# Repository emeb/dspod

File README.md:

# dspod

dspod is a small ecosystem of audio DSP boards

The collection consists of the following hardware

* [dspod_module](./dspod_module) - a motherboard / carrier that adapts the standard dspod pinout
  for Eurorack, including power, I/O level buffers and user interface.
* [dspod_cv1800b](./dspod_cv1800b) - a daughterboard comprising a Sophgo/CVItek CV1800B Linux SoC
  with 64MB RAM, SD card interface, USB and GPIO + audio I/O.
* [dspod_rp2350](./dspod_rp2350) - a daughterboard with a Raspberry Pi RP2350, 4MB flash, 8MB PSRAM, USB, GPIO and audio I/O.
* [dspod_esp32s3](./dspod_esp32s3) - a daughterboard with an ESP32 S3 processor, 4MB flash, 2MB PSRAM, USB, RF, GPIO and audio I/O.
* [dspod_h7r3](./dspod_h7r3) - a daughterboard with an STM32H7R3V8 MCU, QSPI flash or PSRAM, USB, GPIO and audio I/O
* [dspod_u3c5](dspod_u3c5) - a daughterboard with an STM32U3C5RI MCU, QSPI PSRAM, USB, GPIO and audio I/O.
* [dspod_up5k](dspod_up5k) - a daughterboard with an iCE40UP5k FPGA, Flash, PSRAM, ADC, GPIO and audio I/O.
* [dspod_stampp4](./dspod_stampp4) - a daughterboard with an ESP32 P4 MCU, 16MB flash, 32MB PSRAM, USB, GPIO and Audio I/O

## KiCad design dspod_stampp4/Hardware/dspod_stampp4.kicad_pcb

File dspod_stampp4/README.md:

# dspod_stampp4

The dspod_stampp4 is an audio daughterboard based on the M5Stack Stamp P4 which provides an ESP32P4 MCU with 16MB Flash, 32MB PSRAM, USB and GPIO. The M5Stack module is used because the bare ESP32P4 devices were not available from the usual hobbyist distribution channels at the time of development. The primary motivation was to see if the faster dual-core RISC V architecture provided any meaningful performance benefit.

## Abstract

This board is a small 32-pin device with the following features:

* M5Stack Stamp P4 module containing 
  - ESP32S3H4R2 MCU
    - 68-pin QFN package
    - Dual-core RISC V CPUs 
    - 768kB SRAM
    - 32MB PSRAM in package
    - USB, I2C, SPI, ADC, GPIO, etc on-chip
  - 16MB QSPI flash
  - USB-C Connector for development
  - Various connectors for MIPI, SD
* Nuvoton NAU88C22 stereo codec
* Misc GPIO
  - SPI
  - I2C
  - GPIO
* Four channels of 3.3V multiplexed A/D input

## Design Materials

* [Schematic](./doc/dspod_stampp4_sch.pdf)

## Hardware

The hardware design is provided in Kicad 9.x format in the [Hardware](./Hardware) directory.

## Firmware

Firmware is available in the [Firmware](./Firmware) directory.

## Results

The hardware implementation is very similar to the [dspod_esp32s3](../dspod_esp32s3/README.md) so there weren't any big surprises in the overall performance. The encoder/button/LCD-based UI is virtually identical to that on the other three dspod projects so it feels pretty much the same regardless of which instance is in use. The basic effects - filters, delays, reverbs, pitch, frequency and phase shifts - all work the same way and use roughly the right amount of CPU based on their complexity. Some minor changes were required to the ADC and I2S hardware driver code due to the differences between ESP-IDF V5.x and V6.x, as well as migrating from Extensa to RISC-V CPU architecture.

Overall, the faster CPU cores (360MHz RISC V vs 240MHz Extensa LX7 on the ESP32 S3) didn't make a huge difference in DSP performance and the modest speedup in the algorithms that run exclusively from on-chip memory wouldn't be a strong motivator for choosing the P4 vs the S3.

Hardware-wise, using the pre-build module with castellated pads presented some additional assembly challenges, most notably that the module does not fit between the  two rows of pin headers in the dspod physical standard so it was necessary to use SMT pin headers soldered to the bottom side of the board which was difficult to align properly in order to ensure the board would plug into the dspod_module. That aside, having all the small SMT components pre-assembled on the module did make frontside assembly much simpler.

## Going Further

While I've explored most of the highlights, there are a few aspects of this MCU I'd like to explore further:

#### CPU Cores

Pushing the RISC V CPU cores harder and trying some of the more advanced math features would be interesting.

#### Algorithms

The current complement of effects algorithms are fairly lightweight so I'm looking forward to trying out some more complex things, and while spectral processing is probably not practical, there is CPU bandwidth and RAM capacity for more complex time domain effects.

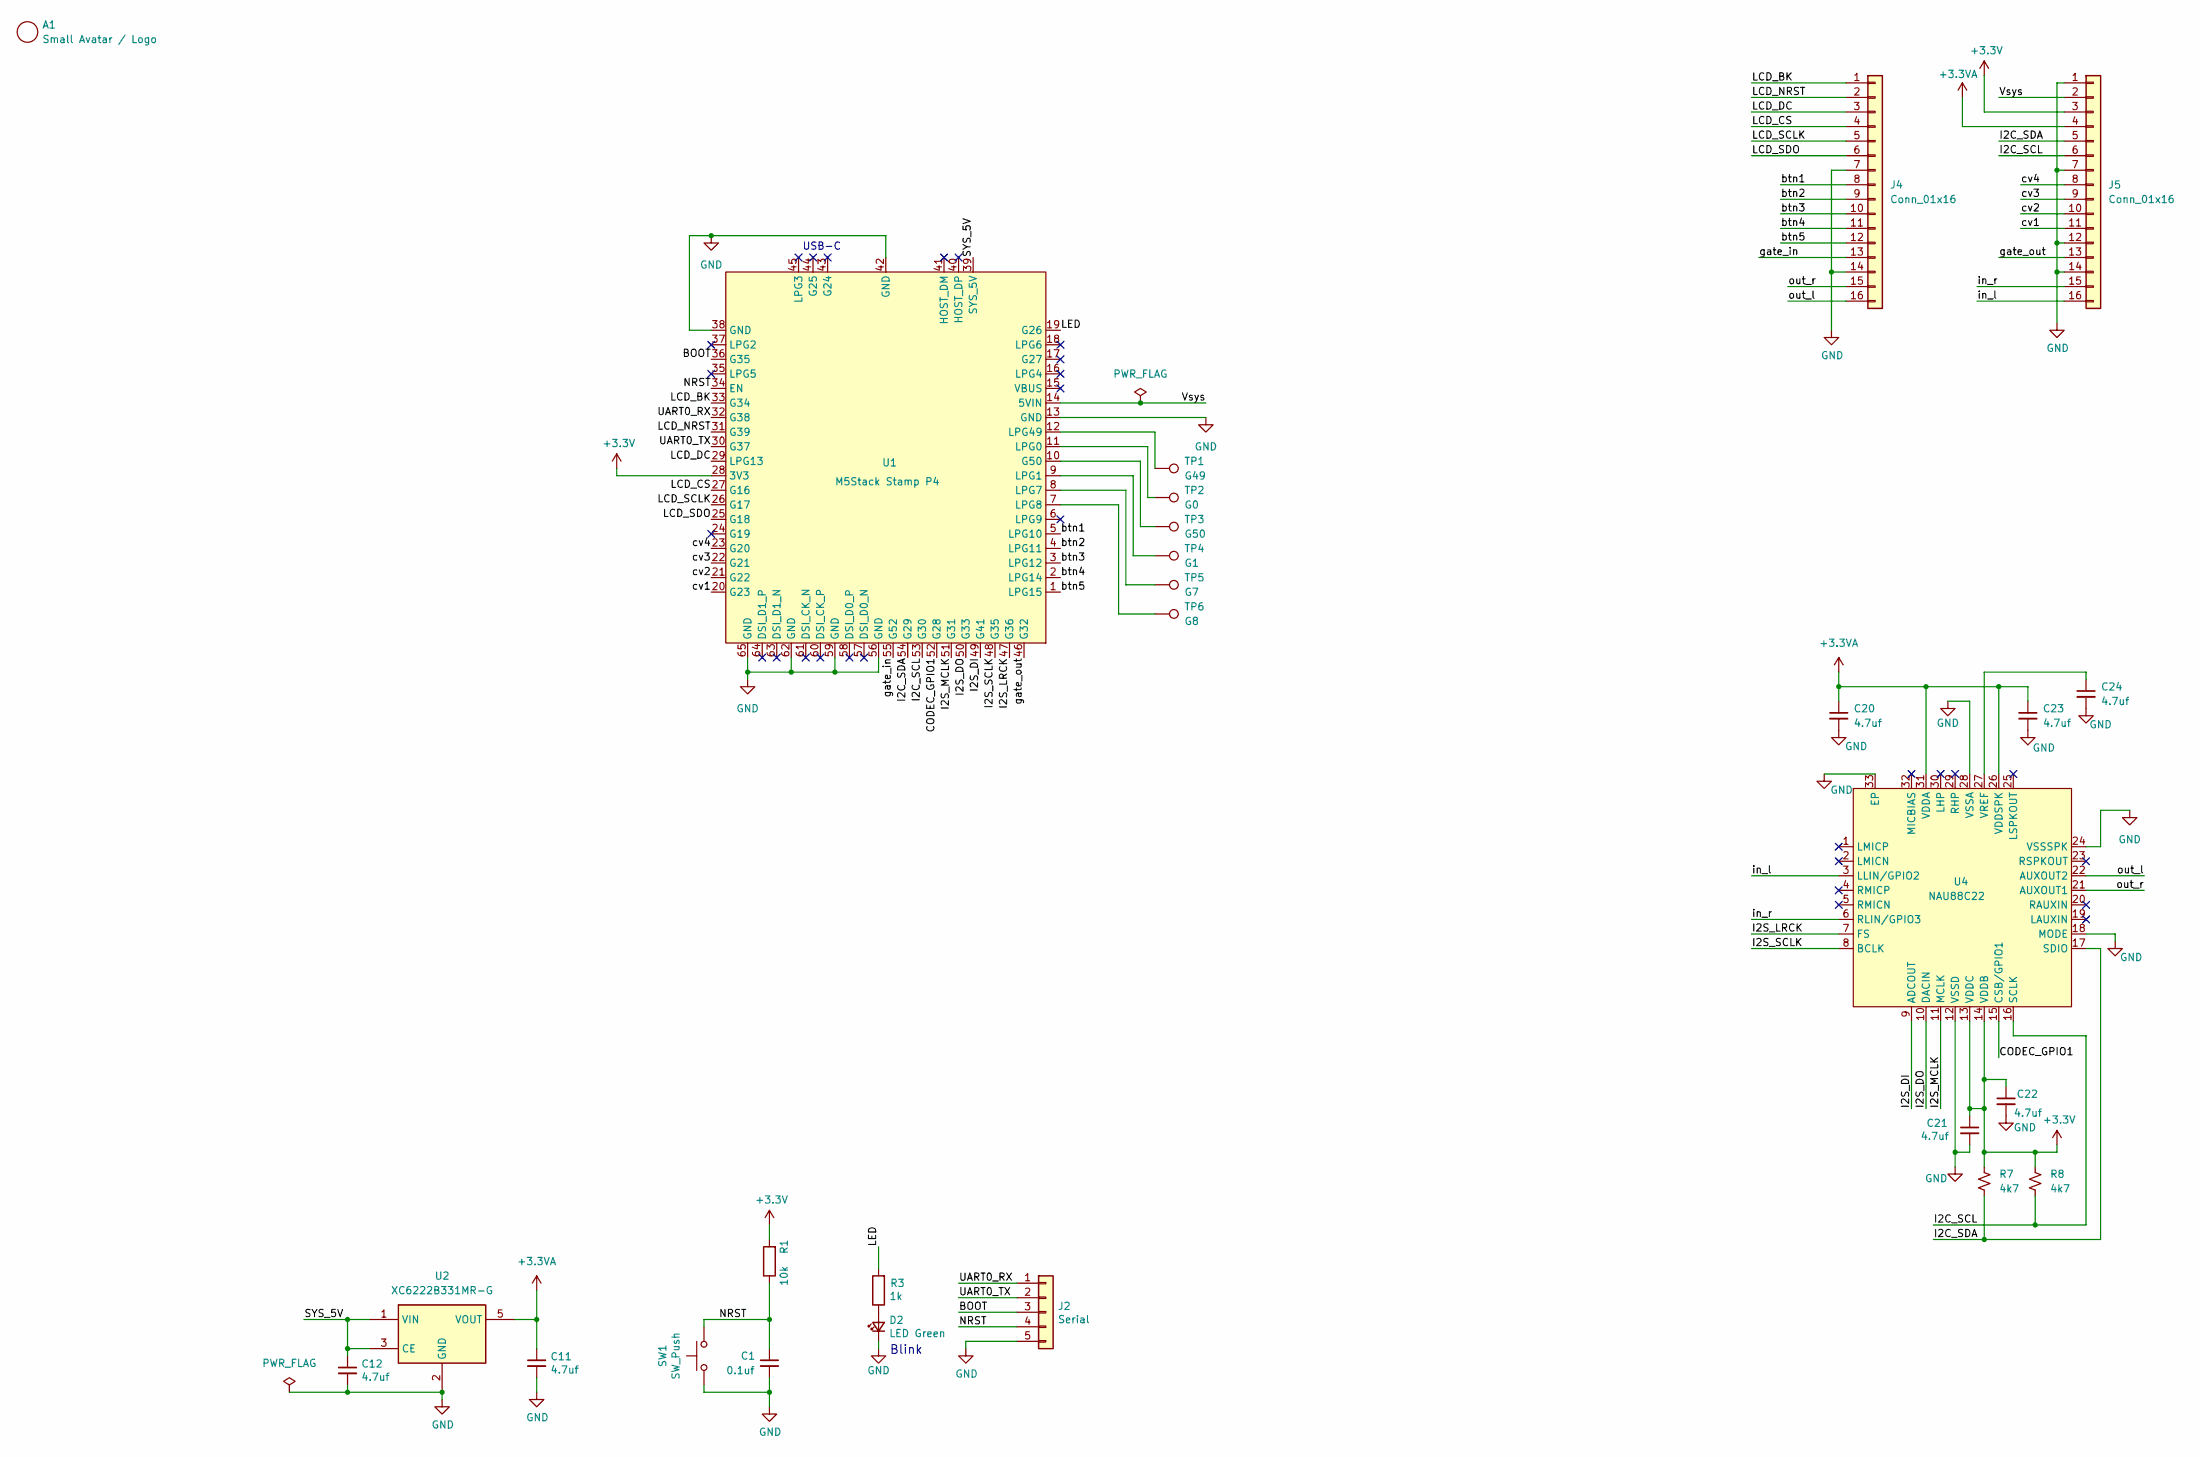
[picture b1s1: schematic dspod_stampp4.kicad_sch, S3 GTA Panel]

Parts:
A1: Small Avatar / Logo; avatar_small
C1: 0.1uf; C_0402_1005Metric
C11, C12, C20, C21, C22, C23, C24: 4.7uf; C_0402_1005Metric
D2: LED Green; LED_0603_1608Metric
J2: Serial; PinHeader_1x05_P2.54mm_Horizontal
J4, J5: Conn_01x16; PinHeader_1x16_P2.54mm_Vertical_SMD_Pin1Left
R1: 10k; R_0402_1005Metric
R3: 1k; R_0402_1005Metric
R7, R8: 4k7; R_0402_1005Metric
SW1: SW_Push; SW_Push_1P1T_NO_CK_KMR2
TP1: G49; TestPoint_Pad_D1.0mm
TP2: G0; TestPoint_Pad_D1.0mm
TP3: G50; TestPoint_Pad_D1.0mm
TP4: G1; TestPoint_Pad_D1.0mm
TP5: G7; TestPoint_Pad_D1.0mm
TP6: G8; TestPoint_Pad_D1.0mm
U1: M5Stack Stamp P4; Stamp-P4
U2: XC6222B331MR-G; SOT-23-5
U4: NAU88C22; QFN-32-1EP_5x5mm_P0.5mm_EP3.1x3.1mm

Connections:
+3.3V: C21.1, C22.1, J5.3, R1.2, R7.2, R8.2, U1.28 (3V3), U4.13 (VDDC), U4.14 (VDDB)
+3.3VA: C11.1, C20.1, C23.1, J5.4, U2.5 (VOUT), U4.26 (VDDSPK), U4.31 (VDDA)
/BOOT: J2.3, U1.36 (G35)
/CODEC_GPIO1: U1.52 (G28), U4.15 (CSB/GPIO1)
/I2C_SCL: J5.6, R8.1, U1.53 (G30), U4.16 (SCLK)
/I2C_SDA: J5.5, R7.1, U1.54 (G29), U4.17 (SDIO)
/I2S_DI: U1.49 (G41), U4.9 (ADCOUT)
/I2S_DO: U1.50 (G33), U4.10 (DACIN)
/I2S_LRCK: U1.47 (G36), U4.7 (FS)
/I2S_MCLK: U1.51 (G31), U4.11 (MCLK)
/I2S_SCLK: U1.48 (G35), U4.8 (BCLK)
/LCD_BK: J4.1, U1.33 (G34)
/LCD_CS: J4.4, U1.27 (G16)
/LCD_DC: J4.3, U1.29 (LPG13)
/LCD_NRST: J4.2, U1.31 (G39)
/LCD_SCLK: J4.5, U1.26 (G17)
/LCD_SDO: J4.6, U1.25 (G18)
/LED: R3.2, U1.19 (G26)
/NRST: C1.1, J2.4, R1.1, SW1.1, U1.34 (EN)
/SYS_5V: C12.1, U1.39 (SYS_5V), U2.1 (VIN), U2.3 (CE)
/UART0_RX: J2.1, U1.32 (G38)
/UART0_TX: J2.2, U1.30 (G37)
/Vsys: J5.2, U1.14 (5VIN)
/btn1: J4.8, U1.5 (LPG10)
/btn2: J4.9, U1.4 (LPG11)
/btn3: J4.10, U1.3 (LPG12)
/btn4: J4.11, U1.2 (LPG14)
/btn5: J4.12, U1.1 (LPG15)
/cv1: J5.11, U1.20 (G23)
/cv2: J5.10, U1.21 (G22)
/cv3: J5.9, U1.22 (G21)
/cv4: J5.8, U1.23 (G20)
/gate_in: J4.13, U1.55 (G52)
/gate_out: J5.13, U1.46 (G32)
/in_l: J5.16, U4.3 (LLIN/GPIO2)
/in_r: J5.15, U4.6 (RLIN/GPIO3)
/out_l: J4.16, U4.22 (AUXOUT2)
/out_r: J4.15, U4.21 (AUXOUT1)
GND: C1.2, C11.2, C12.2, C20.2, C21.2, C22.2, C23.2, C24.2, D2.1 (K), J2.5, J4.7, J4.14, J5.1, J5.7, J5.12, J5.14, SW1.2, U1.13 (GND), U1.38 (GND), U1.42 (GND), U1.56 (GND), U1.59 (GND), U1.62 (GND), U1.65 (GND), U2.2 (GND), U4.12 (VSSD), U4.18 (MODE), U4.24 (VSSSPK), U4.28 (VSSA), U4.33 (EP)
unnamed: D2.2 (A), R3.1
unnamed: TP3.1 (1_1), U1.10 (G50)
unnamed: TP2.1 (1_1), U1.11 (LPG0)
unnamed: TP4.1 (1_1), U1.9 (LPG1)
unnamed: TP5.1 (1_1), U1.8 (LPG7)
unnamed: TP6.1 (1_1), U1.7 (LPG8)
unnamed: TP1.1 (1_1), U1.12 (LPG49)
unnamed: C24.1, U4.27 (VREF)

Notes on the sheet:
Blink
USB-C

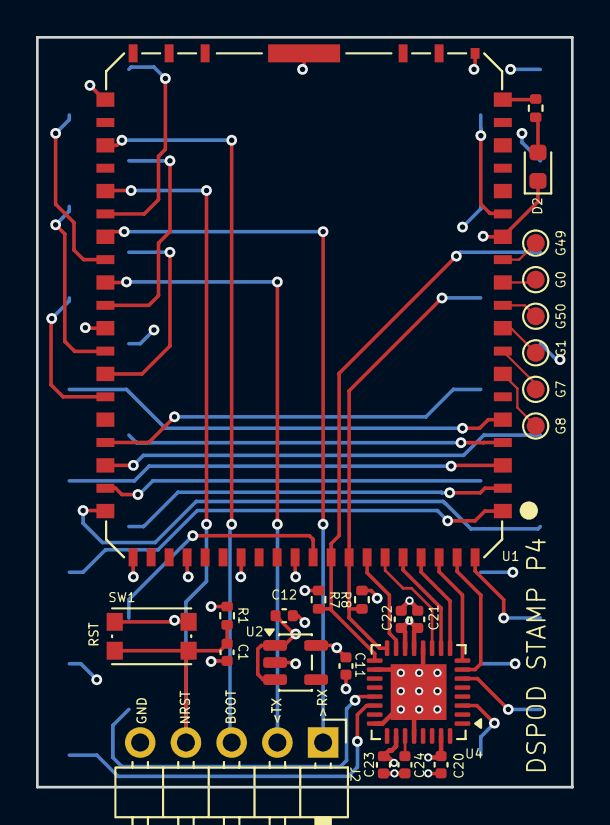
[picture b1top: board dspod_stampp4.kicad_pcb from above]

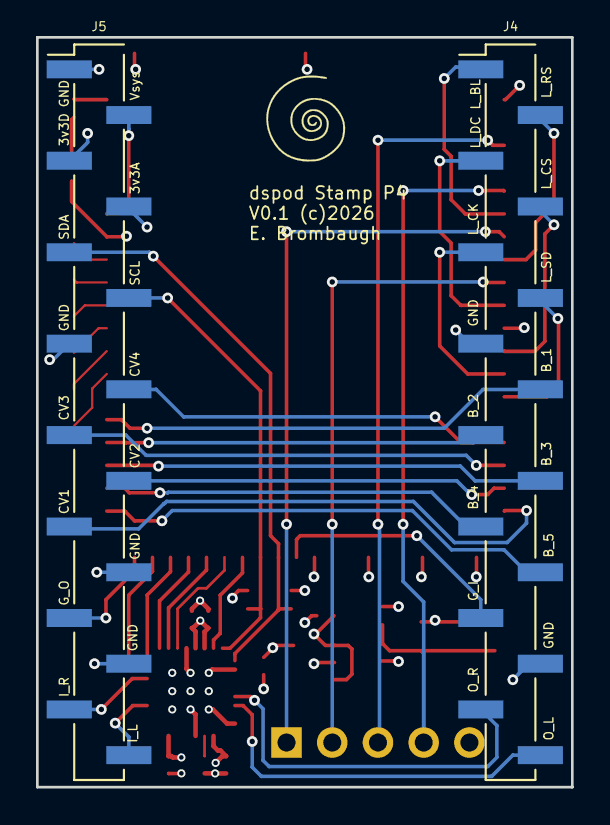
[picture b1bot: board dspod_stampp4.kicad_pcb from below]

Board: 4 copper layers, 29.7 x 41.7 mm, 27 parts (3 on the bottom side), 47 nets.

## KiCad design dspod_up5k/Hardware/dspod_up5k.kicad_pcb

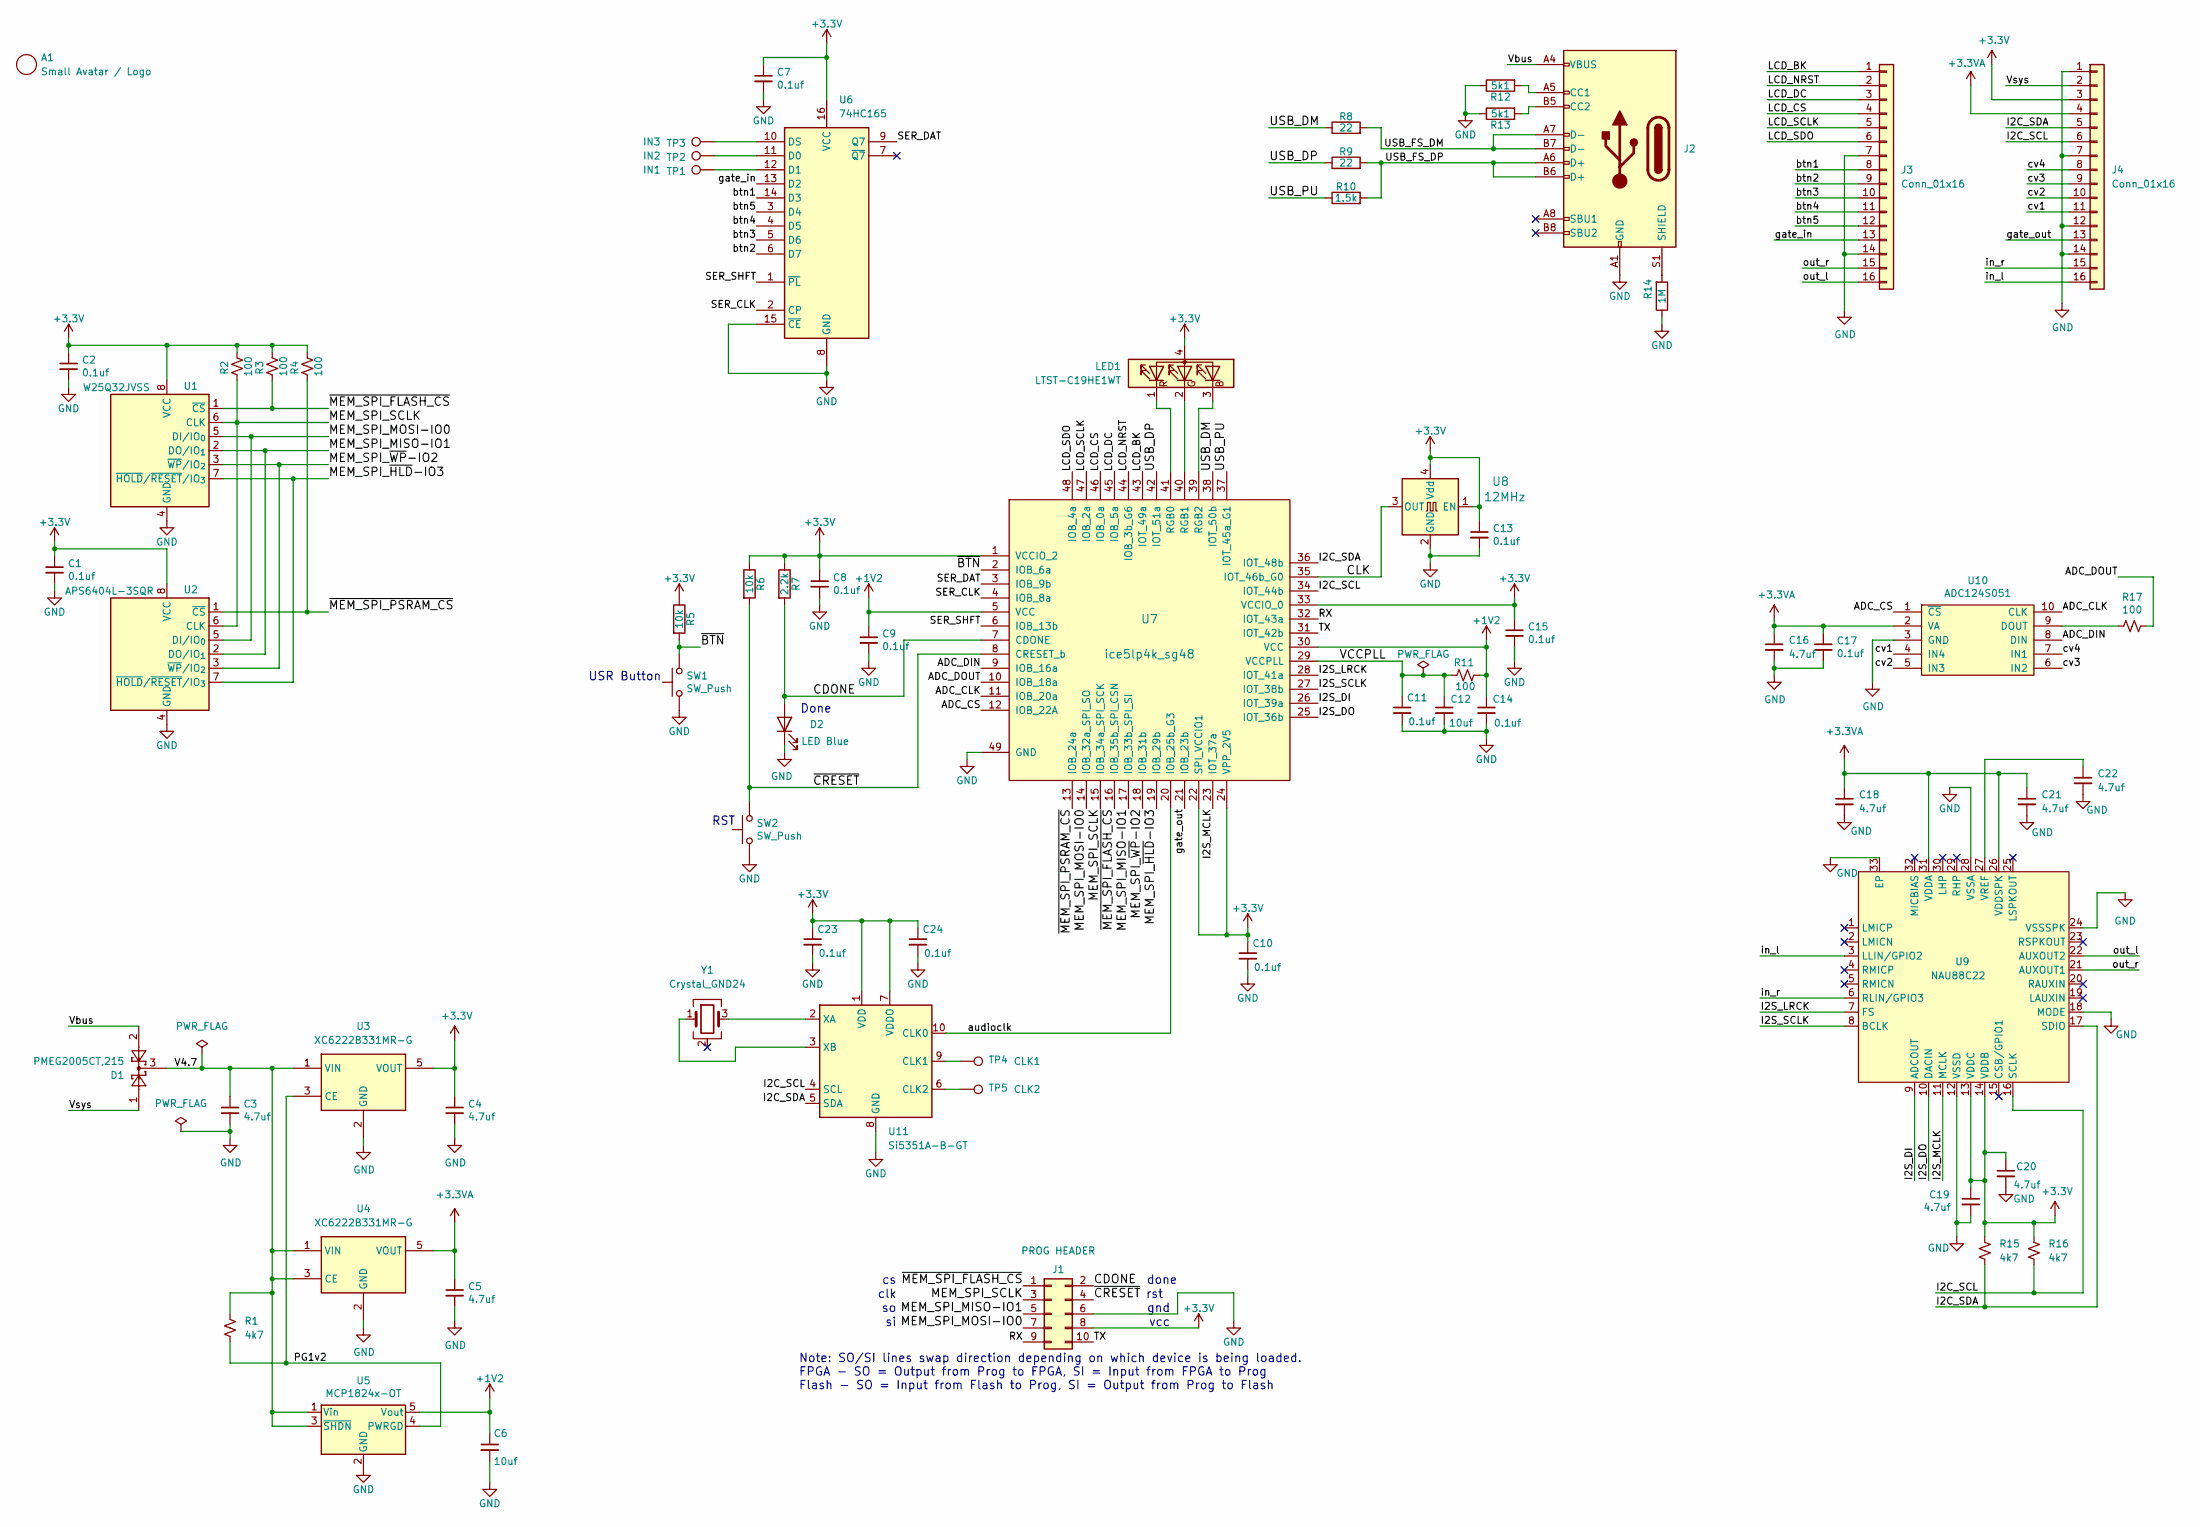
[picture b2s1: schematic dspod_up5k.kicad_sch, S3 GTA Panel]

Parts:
A1: Small Avatar / Logo; avatar_small
C1, C2, C7, C8, C9, C10, C11, C13, C14, C15, C17, C23, C24: 0.1uf; C_0402_1005Metric
C3, C4, C5, C16, C18, C19, C20, C21, C22: 4.7uf; C_0402_1005Metric
C6, C12: 10uf; C_0805_2012Metric
D1: PMEG2005CT,215; SOT-23
D2: LED Blue; LED_0603_1608Metric
J1: PROG HEADER; PinHeader_2x05_P1.27mm_Vertical
J2: USB_C_Receptacle_USB2.0; USB_C_Receptacle_HRO_TYPE-C-31-M-12
J3, J4: Conn_01x16; PinHeader_1x16_P2.54mm_Vertical
LED1: LTST-C19HE1WT; LED_LiteOn_LTST-C19HE1WT
R1, R15, R16: 4k7; R_0402_1005Metric
R2, R3, R4, R11, R17: 100; R_0402_1005Metric
R5, R6: 10k; R_0402_1005Metric
R7: 2.2k; R_0402_1005Metric
R8, R9: 22; R_0402_1005Metric
R10: 1.5k; R_0402_1005Metric
R12, R13: 5k1; R_0402_1005Metric
R14: 1M; R_0402_1005Metric
SW1, SW2: SW_Push; SW_Push_1P1T_NO_CK_KMR2
TP1: IN1; TestPoint_Pad_D1.0mm
TP2: IN2; TestPoint_Pad_D1.0mm
TP3: IN3; TestPoint_Pad_D1.0mm
TP4: CLK1; TestPoint_Pad_D1.0mm
TP5: CLK2; TestPoint_Pad_D1.0mm
U1: W25Q32JVSS; WSON-8-1EP_6x5mm_P1.27mm_EP3.4x4.3mm
U2: APS6404L-3SQR; SOIC-8_3.9x4.9mm_P1.27mm
U3, U4: XC6222B331MR-G; SOT-23-5
U5: MCP1824x-OT; SOT-23-5
U6: 74HC165; TSSOP-16_4.4x5mm_P0.65mm
U7: ice5lp4k_sg48; QFN-48-1EP_7x7mm_Pitch0.5mm_DIY_PADS
U8: 12MHz; Oscillator_SMD_Abracon_ASE-4Pin_3.2x2.5mm
U9: NAU88C22; QFN-32-1EP_5x5mm_P0.5mm_EP3.1x3.1mm
U10: ADC124S051; MSOP-10_3x3mm_P0.5mm
U11: Si5351A-B-GT; MSOP-10_3x3mm_P0.5mm
Y1: Crystal_GND24; Crystal_SMD_3225-4Pin_3.2x2.5mm

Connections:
+1V2: C6.1, C9.1, C14.1, R11.1, U5.5 (Vout), U7.5 (VCC), U7.30 (VCC)
+3.3V: C1.1, C2.1, C4.1, C7.1, C8.1, C10.1, C13.1, C15.1, C19.1, C20.1, C23.1, C24.1, J1.8, J4.3, LED1.4 (A), R2.1, R3.1, R4.1, R5.1, R6.1, R7.1, R15.2, R16.2, U1.8 (VCC), U2.8 (VCC), U3.5 (VOUT), U6.16 (VCC), U7.1 (VCCIO_2), U7.22 (SPI_VCCIO1), U7.24 (VPP_2V5), U7.33 (VCCIO_0), U8.1 (EN), U8.4 (Vdd), U9.13 (VDDC), U9.14 (VDDB), U11.1 (VDD), U11.7 (VDDO)
+3.3VA: C5.1, C16.1, C17.1, C18.1, C21.1, J4.4, U4.5 (VOUT), U9.26 (VDDSPK), U9.31 (VDDA), U10.2 (VA)
/ADC_CLK: U7.11 (IOB_20a), U10.10 (CLK)
/ADC_CS: U7.12 (IOB_22A), U10.1 (~CS)
/ADC_DIN: U7.9 (IOB_16a), U10.8 (DIN)
/ADC_DOUT: R17.1, U7.10 (IOB_18a)
/CDONE: D2.2 (A), J1.2, R7.2, U7.7 (CDONE)
/CLK: U7.35 (IOT_46b_G0), U8.3 (OUT)
/I2C_SCL: J4.6, R16.1, U7.34 (IOT_44b), U9.16 (SCLK), U11.4 (SCL)
/I2C_SDA: J4.5, R15.1, U7.36 (IOT_48b), U9.17 (SDIO), U11.5 (SDA)
/I2S_DI: U7.26 (IOT_39a), U9.9 (ADCOUT)
/I2S_DO: U7.25 (IOT_36b), U9.10 (DACIN)
/I2S_LRCK: U7.28 (IOT_41a), U9.7 (FS)
/I2S_MCLK: U7.23 (IOT_37a), U9.11 (MCLK)
/I2S_SCLK: U7.27 (IOT_38b), U9.8 (BCLK)
/LCD_BK: J3.1, U7.43 (IOT_49a)
/LCD_CS: J3.4, U7.46 (IOB_0a)
/LCD_DC: J3.3, U7.45 (IOB_5a)
/LCD_NRST: J3.2, U7.44 (IOB_3b_G6)
/LCD_SCLK: J3.5, U7.47 (IOB_2a)
/LCD_SDO: J3.6, U7.48 (IOB_4a)
/MEM_SPI_MISO-IO1: J1.5, U1.2 (DO/IO_{1}), U2.2 (DO/IO_{1}), U7.17 (IOB_33b_SPI_SI)
/MEM_SPI_MOSI-IO0: J1.7, U1.5 (DI/IO_{0}), U2.5 (DI/IO_{0}), U7.14 (IOB_32a_SPI_SO)
/MEM_SPI_SCLK: J1.3, R2.2, U1.6 (CLK), U2.6 (CLK), U7.15 (IOB_34a_SPI_SCK)
/MEM_SPI_~HLD-IO3: U1.7 (~HOLD/~RESET/IO_{3}), U2.7 (~HOLD/~RESET/IO_{3}), U7.19 (IOB_29b)
/MEM_SPI_~WP-IO2: U1.3 (~WP/IO_{2}), U2.3 (~WP/IO_{2}), U7.18 (IOB_31b)
/PG1v2: R1.1, U3.3 (CE), U5.4 (PWRGD)
/RX: J1.9, U7.32 (IOT_43a)
/SER_CLK: U6.2 (CP), U7.4 (IOB_8a)
/SER_DAT: U6.9 (Q7), U7.3 (IOB_9b)
/SER_SHFT: U6.1 (~PL), U7.6 (IOB_13b)
/TX: J1.10, U7.31 (IOT_42b)
/USB_DM: R8.1, U7.38 (IOT_50b)
/USB_DP: R9.1, U7.42 (IOT_51a)
/USB_FS_DM: J2.A7 (D-), J2.B7 (D-), R8.2
/USB_FS_DP: J2.A6 (D+), J2.B6 (D+), R9.2, R10.2
/USB_PU: R10.1, U7.37 (IOT_45a_G1)
/V4.7: C3.1, D1.3, R1.2, U3.1 (VIN), U4.1 (VIN), U4.3 (CE), U5.1 (Vin), U5.3 (~SHDN)
/VCCPLL: C11.1, C12.1, R11.2, U7.29 (VCCPLL)
/Vbus: D1.2, J2.A4 (VBUS), J2.A9 (VBUS), J2.B4 (VBUS), J2.B9 (VBUS)
/Vsys: D1.1, J4.2
/audioclk: U7.20 (IOB_25b_G3), U11.10 (CLK0)
/btn1: J3.8, U6.14 (D3)
/btn2: J3.9, U6.6 (D7)
/btn3: J3.10, U6.5 (D6)
/btn4: J3.11, U6.4 (D5)
/btn5: J3.12, U6.3 (D4)
/cv1: J4.11, U10.4 (IN4)
/cv2: J4.10, U10.5 (IN3)
/cv3: J4.9, U10.6 (IN2)
/cv4: J4.8, U10.7 (IN1)
/gate_in: J3.13, U6.13 (D2)
/gate_out: J4.13, U7.21 (IOB_23b)
/in_l: J4.16, U9.3 (LLIN/GPIO2)
/in_r: J4.15, U9.6 (RLIN/GPIO3)
/out_l: J3.16, U9.22 (AUXOUT2)
/out_r: J3.15, U9.21 (AUXOUT1)
/~BTN: R5.2, SW1.2, U7.2 (IOB_6a)
/~CRESET: J1.4, R6.2, SW2.2, U7.8 (CRESET_b)
/~MEM_SPI_FLASH_CS: J1.1, R3.2, U1.1 (~CS), U7.16 (IOB_35b_SPI_CSN)
/~MEM_SPI_PSRAM_CS: R4.2, U2.1 (~CS), U7.13 (IOB_24a)
GND: C1.2, C2.2, C3.2, C4.2, C5.2, C6.2, C7.2, C8.2, C9.2, C10.2, C11.2, C12.2, C13.2, C14.2, C15.2, C16.2, C17.2, C18.2, C19.2, C20.2, C21.2, C22.2, C23.2, C24.2, D2.1 (K), J1.6, J2.A1 (GND), J2.A12 (GND), J2.B1 (GND), J2.B12 (GND), J3.7, J3.14, J4.1, J4.7, J4.12, J4.14, R12.1, R13.1, R14.1, SW1.1, SW2.1, U1.4 (GND), U2.4 (GND), U3.2 (GND), U4.2 (GND), U5.2 (GND), U6.8 (GND), U6.15 (~CE), U7.49 (GND), U8.2 (GND), U9.12 (VSSD), U9.18 (MODE), U9.24 (VSSSPK), U9.28 (VSSA), U9.33 (EP), U10.3 (GND), U11.8 (GND)
unnamed: J2.A5 (CC1), R12.2
unnamed: J2.B5 (CC2), R13.2
unnamed: J2.S1 (SHIELD), R14.2
unnamed: LED1.3 (BK), U7.39 (RGB2)
unnamed: LED1.2 (GK), U7.40 (RGB1)
unnamed: LED1.1 (RK), U7.41 (RGB0)
unnamed: TP2.1, U6.11 (D0)
unnamed: TP1.1, U6.12 (D1)
unnamed: TP3.1, U6.10 (DS)
unnamed: C22.1, U9.27 (VREF)
unnamed: R17.2, U10.9 (DOUT)
unnamed: TP4.1, U11.9 (CLK1)
unnamed: TP5.1, U11.6 (CLK2)
unnamed: U11.2 (XA), Y1.3
unnamed: U11.3 (XB), Y1.1

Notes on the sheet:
done
vcc
gnd
USR Button
RST
Done
Note: SO/SI lines swap direction depending on which device is being loaded. FPGA - SO = Output from Prog to FPGA, SI = Input from FPGA to Prog Flash - SO = Input from Flash to Prog, SI = Output from Prog to Flash
rst
clk

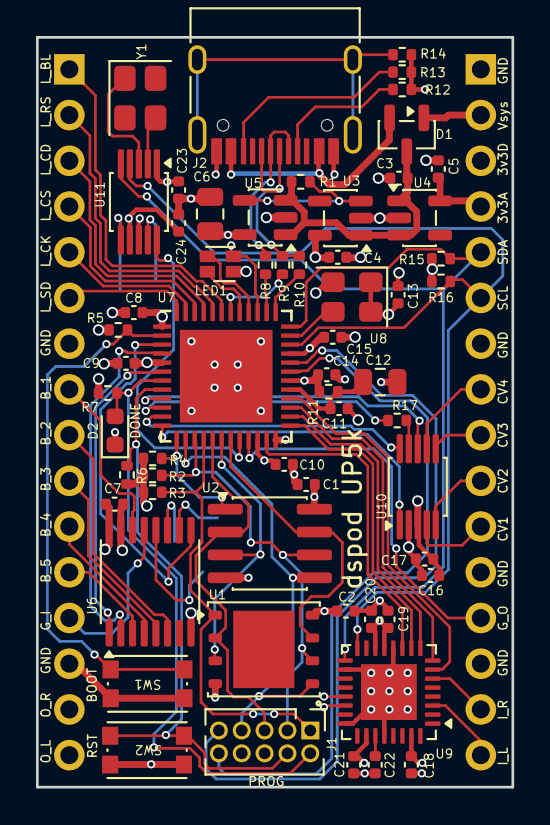
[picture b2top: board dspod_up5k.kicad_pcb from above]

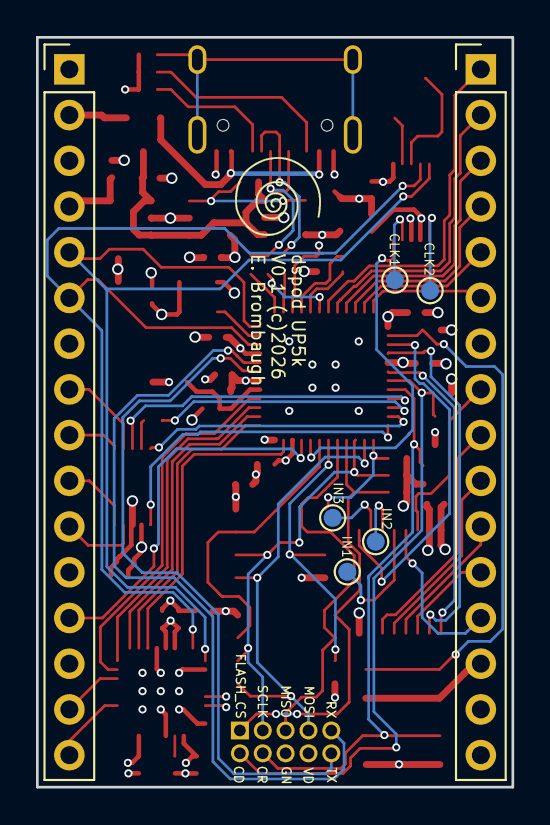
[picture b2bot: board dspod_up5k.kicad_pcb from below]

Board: 4 copper layers, 26.4 x 41.7 mm, 68 parts (8 on the bottom side), 78 nets.

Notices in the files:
dspod_cv1800b/Hardware/dspod_cv1800b.kicad_pcb:
V0.1 (c)2025
dspod_module/Hardware/dspod_module.kicad_pcb:
(c) 2025 E. Brombaugh
dspod_stampp4/Hardware/dspod_stampp4.kicad_pcb:
V0.1 (c)2026
parts and their libraries:
Copyright 2021 Accelerated Designs. All rights reserved.
